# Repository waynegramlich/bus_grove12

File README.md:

bus_grove12
===========

Bus with 12 Grove connectors on it.

## Rev. A Issues

* The grove mounting holes are too big.

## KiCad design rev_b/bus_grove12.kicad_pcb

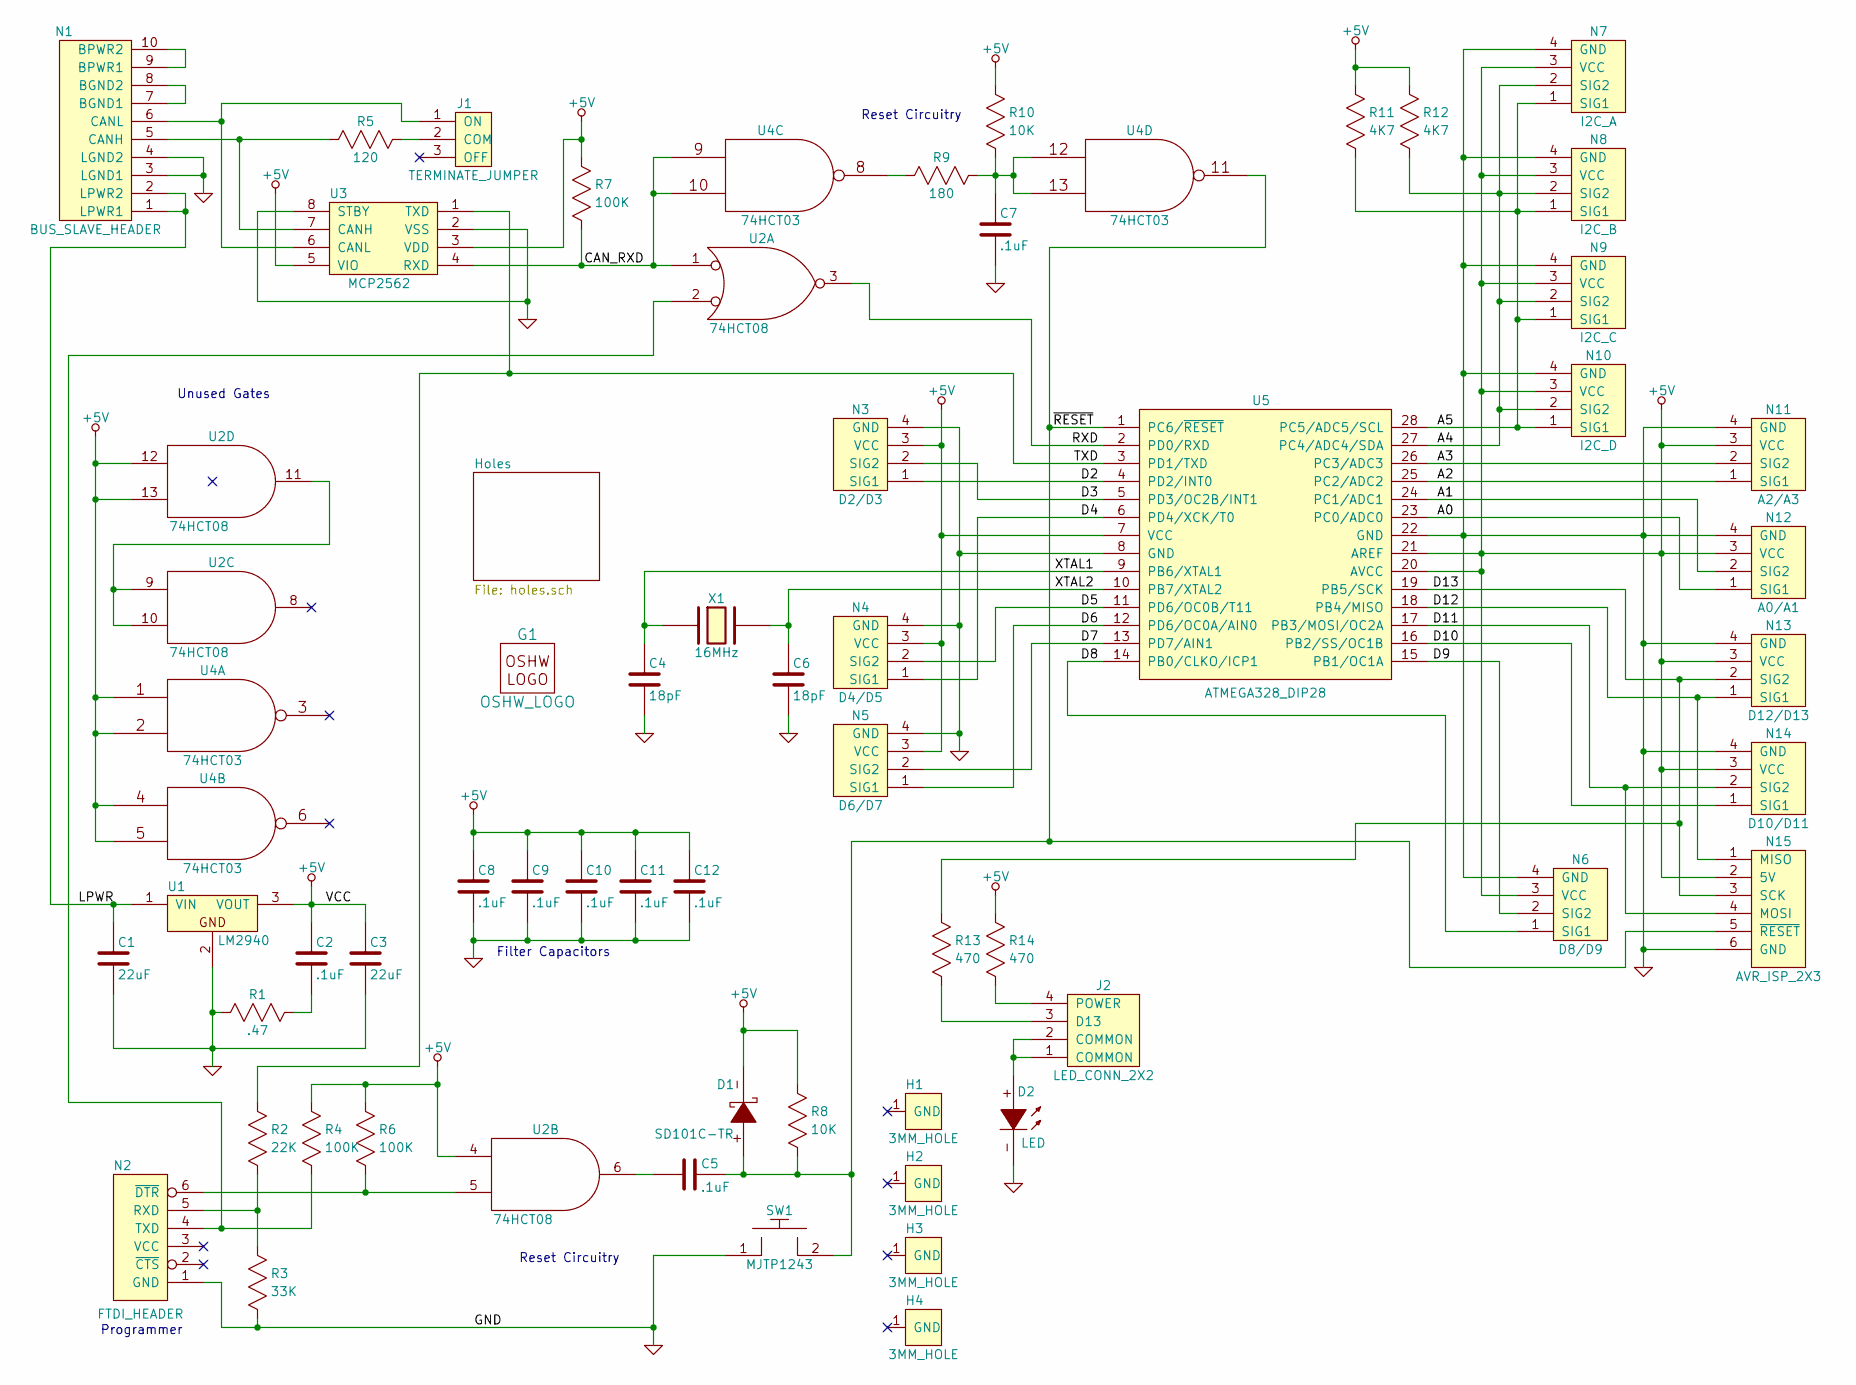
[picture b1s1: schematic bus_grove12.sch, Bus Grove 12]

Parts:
C1, C3: 22uF; Capacitor3MMDiscRM2.5
C2, C5, C7, C8, C9, C10, C11, C12: .1uF; Capacitor4x3RM2-5_RevB
C4, C6: 18pF; Capacitor4x3RM2-5_RevB
D1: SD101C-TR; Diode_DO-41_SOD81_Horizontal_RM10
D2: LED; T1_LED
G1: OSHW_LOGO; OSHW_LOGO_400mil
H1, H2, H3, H4: 3MM_HOLE; MountingHole_3mm
J1: TERMINATE_JUMPER; Pin_Header_Straight_1x03
J2: LED_CONN_2X2; Pin_Header_Straight_2x02
N1: BUS_SLAVE_HEADER; Pin_Header_Straight_2x05_Shrouded
N2: FTDI_HEADER
N3: D2/D3; Grove_Connector
N4: D4/D5; Grove_Connector
N5: D6/D7; Grove_Connector
N6: D8/D9; Grove_Connector
N7: I2C_A; Grove_Connector
N8: I2C_B; Grove_Connector
N9: I2C_C; Grove_Connector
N10: I2C_D; Grove_Connector
N11: A2/A3; Grove_Connector
N12: A0/A1; Grove_Connector
N13: D12/D13; Grove_Connector
N14: D10/D11; Grove_Connector
N15: AVR_ISP_2X3; Pin_Header_Straight_2x03
R1: .47; Resistor_Horizontal_400
R2: 22K; Resistor_Horizontal_400
R3: 33K; Resistor_Horizontal_400
R4, R6, R7: 100K; Resistor_Horizontal_400
R5: 120; Resistor_Horizontal_400
R8, R10: 10K; Resistor_Horizontal_400
R9: 180; Resistor_Horizontal_400
R11, R12: 4K7; Resistor_Horizontal_400
R13, R14: 470; Resistor_Horizontal_400
SW1: MJTP1243; Button_6.5MM
U1: LM2940; TO-220_Neutral123_Horizontal_LargePads
U2: 74HCT08; DIP-14__300
U3: MCP2562; DIP-8__300
U4: 74HCT03; DIP-14__300
U5: ATMEGA328_DIP28; DIP-28__300
X1: 16MHz; Crystal_HC49-U_Vertical

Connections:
+5V: C2.1, C3.1, C8.1, C9.1, C10.1, C11.1, C12.1, D1.-, N3.3 (VCC), N4.3 (VCC), N5.3 (VCC), N6.3 (VCC), N7.3 (VCC), N8.3 (VCC), N9.3 (VCC), N10.3 (VCC), N11.3 (VCC), N12.3 (VCC), N13.3 (VCC), N14.3 (VCC), N15.2 (5V), R4.2, R6.2, R7.2, R8.2, R10.2, R11.2, R12.2, R14.2, U1.3 (VOUT), U2.4, U2.12, U2.13, U2.14 (VCC), U3.3 (VDD), U3.5 (VIO), U4.1, U4.2, U4.4, U4.5, U4.14 (VCC), U5.7 (VCC), U5.20 (AVCC), U5.21 (AREF)
/A0: N12.1 (SIG1), U5.23 (PC0/ADC0)
/A1: N12.2 (SIG2), U5.24 (PC1/ADC1)
/A2: N11.1 (SIG1), U5.25 (PC2/ADC2)
/A3: N11.2 (SIG2), U5.26 (PC3/ADC3)
/A4: N7.2 (SIG2), N8.2 (SIG2), N9.2 (SIG2), N10.2 (SIG2), R12.1, U5.27 (PC4/ADC4/SDA)
/A5: N7.1 (SIG1), N8.1 (SIG1), N9.1 (SIG1), N10.1 (SIG1), R11.1, U5.28 (PC5/ADC5/SCL)
/CAN_RXD: R7.1, U2.1, U3.4 (RXD), U4.9, U4.10
/D2: N3.1 (SIG1), U5.4 (PD2/INT0)
/D3: N3.2 (SIG2), U5.5 (PD3/OC2B/INT1)
/D4: N4.1 (SIG1), U5.6 (PD4/XCK/T0)
/D5: N4.2 (SIG2), U5.11 (PD6/OC0B/T11)
/D6: N5.1 (SIG1), U5.12 (PD6/OC0A/AIN0)
/D7: N5.2 (SIG2), U5.13 (PD7/AIN1)
/D8: N6.1 (SIG1), U5.14 (PB0/CLKO/ICP1)
/D9: N6.2 (SIG2), U5.15 (PB1/OC1A)
/D10: N14.1 (SIG1), U5.16 (PB2/SS/OC1B)
/D11: N14.2 (SIG2), N15.4 (MOSI), U5.17 (PB3/MOSI/OC2A)
/D12: N13.1 (SIG1), N15.1 (MISO), U5.18 (PB4/MISO)
/D13: N13.2 (SIG2), N15.3 (SCK), R13.2, U5.19 (PB5/SCK)
/LPWR: C1.1, N1.1 (LPWR1), N1.2 (LPWR2), U1.1 (VIN)
/RXD: U2.3, U5.2 (PD0/RXD)
/TXD: R2.2, U3.1 (TXD), U5.3 (PD1/TXD)
/XTAL1: C4.1, U5.9 (PB6/XTAL1), X1.1
/XTAL2: C6.1, U5.10 (PB7/XTAL2), X1.2
/~RESET: C5.2, D1.+, N15.5 (~RESET), R8.1, SW1.2, U4.11, U5.1 (PC6/~RESET)
GND: C1.2, C3.2, C4.2, C6.2, C7.2, C8.2, C9.2, C10.2, C11.2, C12.2, D2.-, N1.3 (LGND1), N1.4 (LGND2), N2.1 (GND), N3.4 (GND), N4.4 (GND), N5.4 (GND), N6.4 (GND), N7.4 (GND), N8.4 (GND), N9.4 (GND), N10.4 (GND), N11.4 (GND), N12.4 (GND), N13.4 (GND), N14.4 (GND), N15.6 (GND), R1.1, R3.1, SW1.1, U1.2, U2.7 (GND), U3.2 (VSS), U3.8 (STBY), U4.7 (GND), U5.8 (GND), U5.22 (GND)
unnamed: C2.2, R1.2
unnamed: C5.1, U2.6
unnamed: C7.1, R9.2, R10.1, U4.12, U4.13
unnamed: D2.+, J2.1 (COMMON), J2.2 (COMMON)
unnamed: J1.1 (ON), N1.6 (CANL), U3.6 (CANL)
unnamed: J1.2 (COM), R5.2
unnamed: J2.3 (D13), R13.1
unnamed: J2.4 (POWER), R14.1
unnamed: N1.5 (CANH), R5.1, U3.7 (CANH)
unnamed: N1.7 (BGND1), N1.8 (BGND2)
unnamed: N1.9 (BPWR1), N1.10 (BPWR2)
unnamed: N2.4 (TXD), R4.1, U2.2
unnamed: N2.5 (RXD), R2.1, R3.2
unnamed: N2.6 (~DTR), R6.1, U2.5
unnamed: R9.1, U4.8
unnamed: U2.9, U2.10, U2.11

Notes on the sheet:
Filter Capacitors
Reset Circuitry
Programmer
Unused Gates

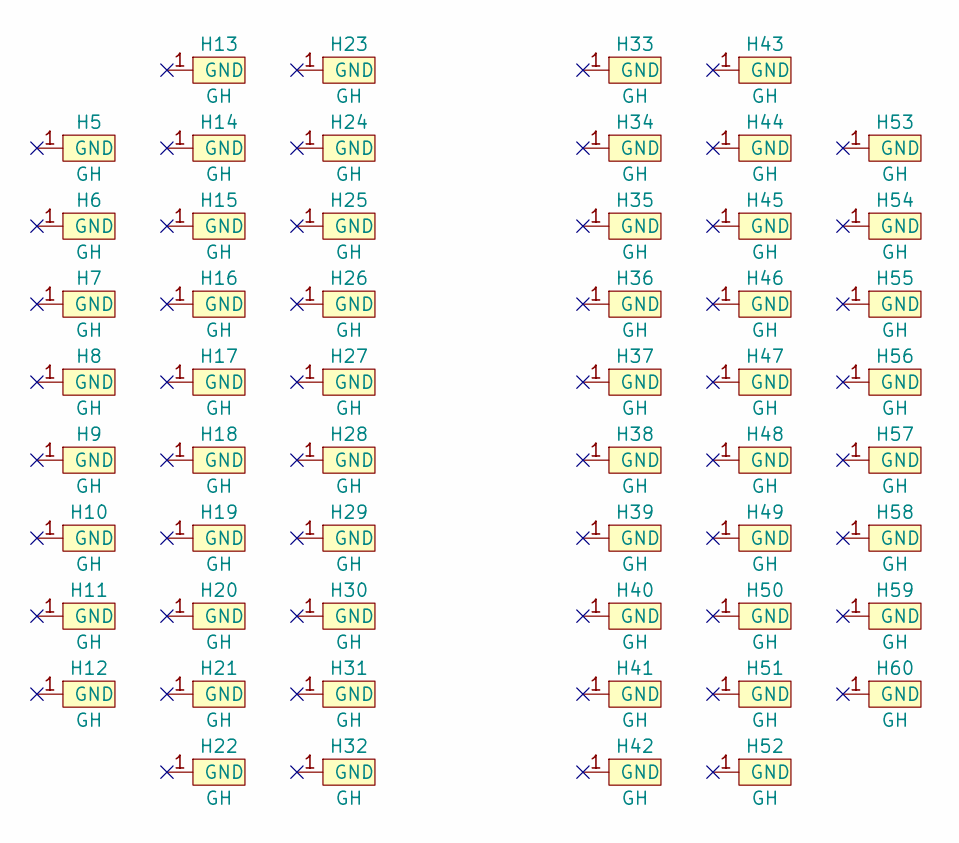
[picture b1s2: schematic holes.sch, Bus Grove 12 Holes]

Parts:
H5, H6, H7, H8, H9, H10, H11, H12, H13, H14, H15, H16, H17, H18, H19, H20, H21, H22, H23, H24, H25, H26, H27, H28, H29, H30, H31, H32, H33, H34, H35, H36, H37, H38, H39, H40, H41, H42, H43, H44, H45, H46, H47, H48, H49, H50, H51, H52, H53, H54, H55, H56, H57, H58, H59, H60: GH; Grove_Hole

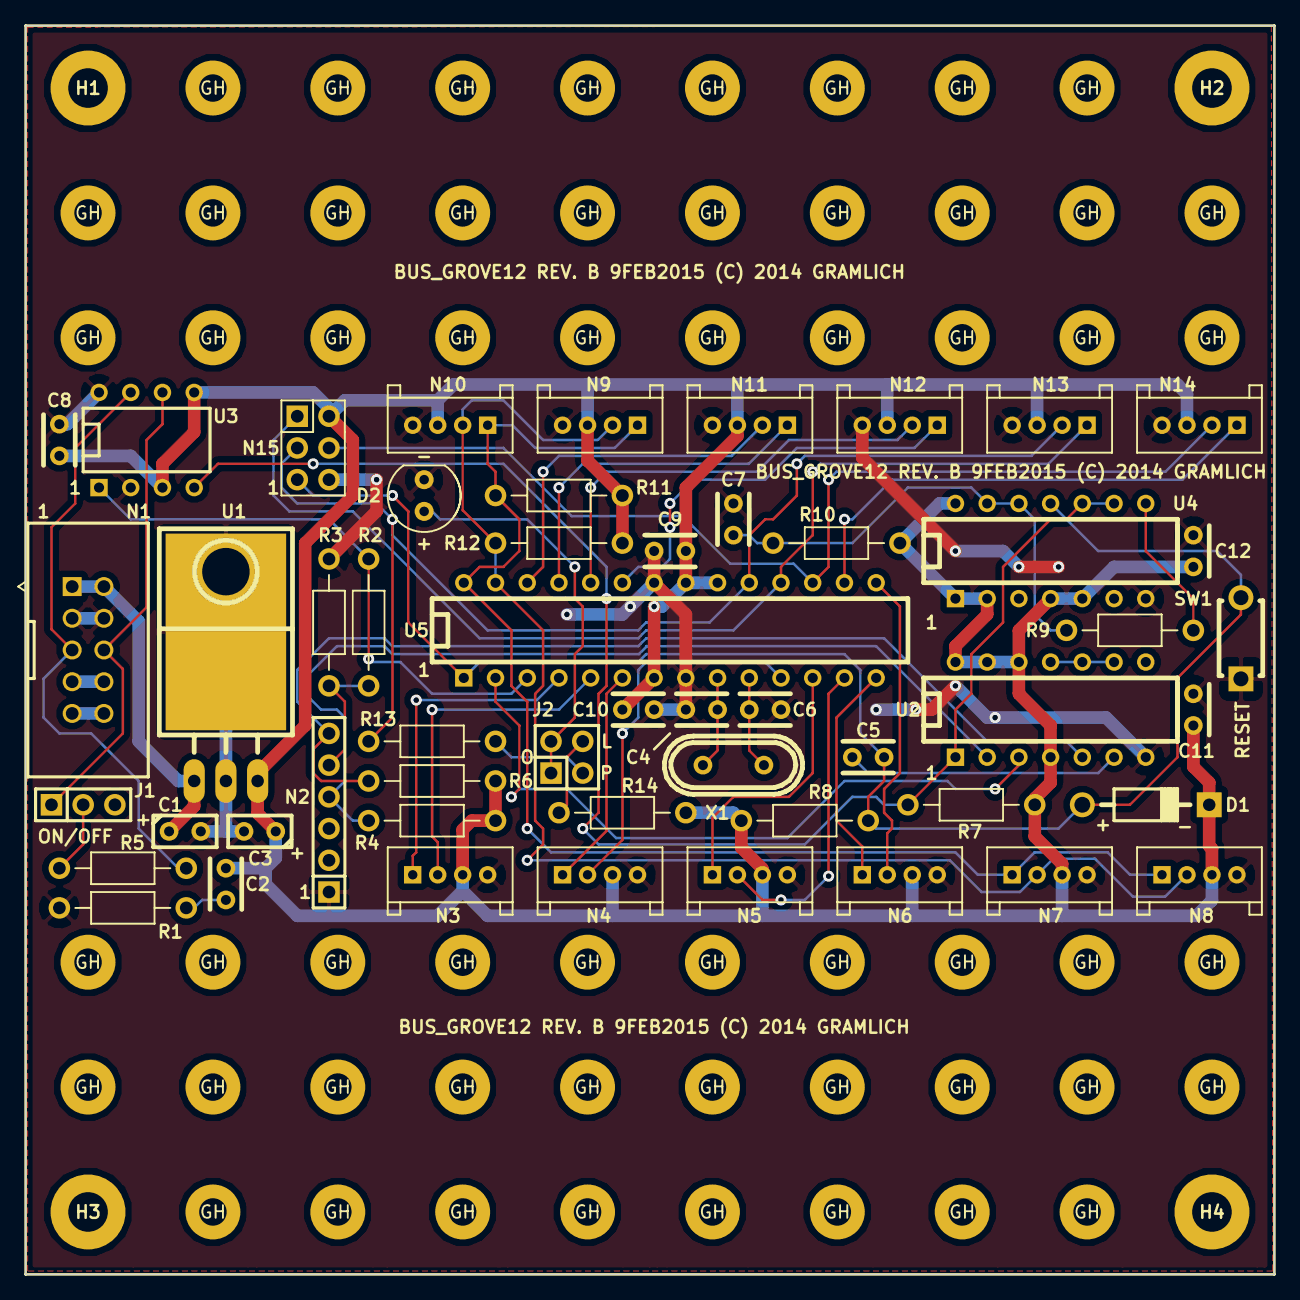
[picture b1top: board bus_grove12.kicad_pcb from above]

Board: 2 copper layers, 100.0 x 100.0 mm, 113 parts (1 on the bottom side), 43 nets.

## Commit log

2014-11-03 Wrapped Rev. A.
2014-11-16 Added Rev. A issues to README.md
2015-02-09 Made a clone of Rev. A
2015-02-09 Rev. B is ready.
2015-02-13 Split 22uF capacitor into tantalum and aluminum.

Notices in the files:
rev_b/bus_grove12.kicad_pcb:
BUS_GROVE12 REV. B 9FEB2015 (C) 2014 GRAMLICH
